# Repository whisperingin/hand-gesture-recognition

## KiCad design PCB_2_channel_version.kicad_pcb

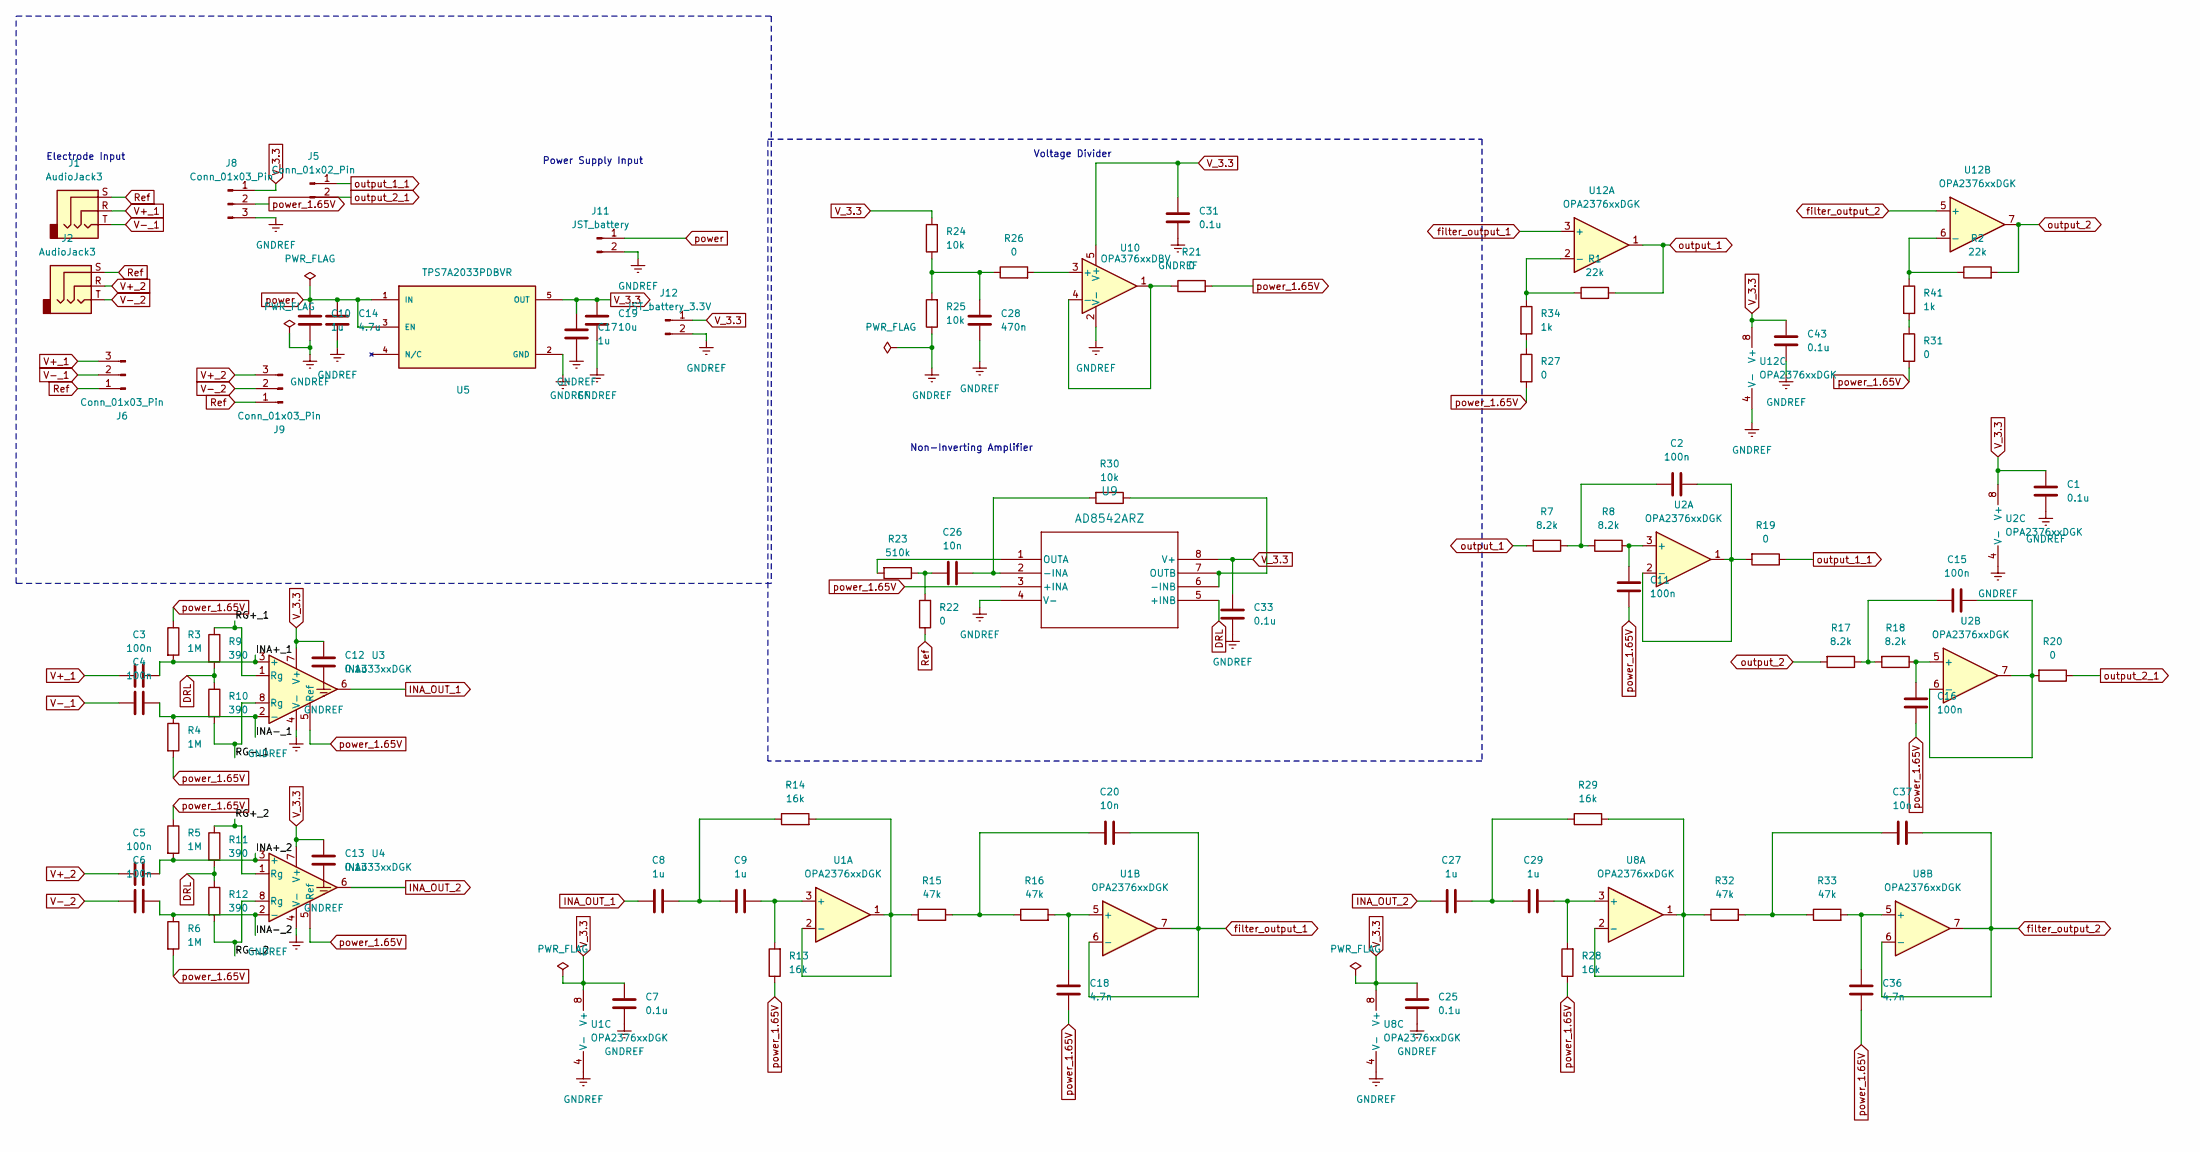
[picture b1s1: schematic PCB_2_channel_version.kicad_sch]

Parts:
C1, C7, C12, C13, C25, C31, C33, C43: 0.1u; C_0603_1608Metric_Pad1.08x0.95mm_HandSolder
C2, C11, C15, C16: 100n; C_0603_1608Metric_Pad1.08x0.95mm_HandSolder
C3, C4, C5, C6: 100n; C_0805_2012Metric_Pad1.18x1.45mm_HandSolder
C8, C9, C10, C17, C27, C29: 1u; C_0805_2012Metric_Pad1.18x1.45mm_HandSolder
C14: 4.7u; C_0805_2012Metric_Pad1.18x1.45mm_HandSolder
C18, C36: 4.7n; C_0805_2012Metric_Pad1.18x1.45mm_HandSolder
C19: 10u; C_0805_2012Metric_Pad1.18x1.45mm_HandSolder
C20, C26, C37: 10n; C_0805_2012Metric_Pad1.18x1.45mm_HandSolder
C28: 470n; C_0603_1608Metric_Pad1.08x0.95mm_HandSolder
J1, J2: AudioJack3; Jack_3.5mm_CUI_SJ-3523-SMT_Horizontal
J5: Conn_01x02_Pin; PinHeader_1x02_P2.54mm_Vertical
J6, J9: Conn_01x03_Pin; JST_PH_S3B-PH-K_1x03_P2.00mm_Horizontal
J8: Conn_01x03_Pin; PinHeader_1x03_P2.54mm_Vertical
J11: JST_battery; JST_PH_B2B-PH-K_1x02_P2.00mm_Vertical
J12: JST_battery_3.3V; JST_PH_B2B-PH-K_1x02_P2.00mm_Vertical
R1, R2: 22k; R_0805_2012Metric_Pad1.20x1.40mm_HandSolder
R3, R4, R5, R6: 1M; R_0805_2012Metric_Pad1.20x1.40mm_HandSolder
R7, R8, R17, R18: 8.2k; R_0603_1608Metric_Pad0.98x0.95mm_HandSolder
R9, R10, R11, R12: 390; R_0805_2012Metric_Pad1.20x1.40mm_HandSolder
R13, R14, R28, R29: 16k; R_0805_2012Metric_Pad1.20x1.40mm_HandSolder
R15, R16, R32, R33: 47k; R_0805_2012Metric_Pad1.20x1.40mm_HandSolder
R19, R20, R21, R22, R26: 0; R_0603_1608Metric_Pad0.98x0.95mm_HandSolder
R23: 510k; R_0805_2012Metric_Pad1.20x1.40mm_HandSolder
R24, R25: 10k; R_0603_1608Metric_Pad0.98x0.95mm_HandSolder
R27, R31: 0; R_0805_2012Metric_Pad1.20x1.40mm_HandSolder
R30: 10k; R_0805_2012Metric_Pad1.20x1.40mm_HandSolder
R34, R41: 1k; R_0805_2012Metric_Pad1.20x1.40mm_HandSolder
U1, U2, U8, U12: OPA2376xxDGK; DGK8
U3, U4: INA333xxDGK; VSSOP-8_3x3mm_P0.65mm
U5: TPS7A2033PDBVR; DBV0005A-IPC_B
U9: AD8542ARZ; R_8_ADI
U10: OPA376xxDBV; SOT-23-5

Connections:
/INA+_1: C3.1, R3.2, U3.3 (+)
/INA+_2: C5.1, R5.2, U4.3 (+)
/INA-_1: C4.1, R4.1, U3.2 (-)
/INA-_2: C6.1, R6.1, U4.2 (-)
/RG+_1: R9.1, U3.1 (Rg)
/RG+_2: R11.1, U4.1 (Rg)
/RG-_1: R10.2, U3.8 (Rg)
/RG-_2: R12.2, U4.8 (Rg)
DRL: R9.2, R10.1, R11.2, R12.1, U9.5 (+INB)
GNDREF: C1.2, C7.2, C10.2, C12.2, C13.2, C14.2, C17.2, C19.2, C25.2, C28.2, C31.2, C33.2, C43.2, J8.3, J11.2, J12.2, R25.1, U1.4 (V-), U2.4 (V-), U3.4 (V-), U4.4 (V-), U5.2 (GND), U8.4 (V-), U9.4 (V-), U10.2 (V-), U12.4 (V-)
INA_OUT_1: C8.2, U3.6
INA_OUT_2: C27.2, U4.6
unnamed: C2.1, R7.1, R8.2
unnamed: C8.1, C9.2, R14.1
unnamed: C15.1, R17.1, R18.2
unnamed: C20.2, R15.2, R16.1
unnamed: C26.2, R22.2, R23.1
unnamed: C27.1, C29.2, R29.1
unnamed: C28.1, R24.1, R25.2, R26.1
unnamed: C37.2, R32.2, R33.1
unnamed: R27.1, R34.2
unnamed: R31.1, R41.2
unnamed: C9.1, R13.2, U1.3 (+)
unnamed: R14.2, R15.1, U1.1, U1.2 (-)
unnamed: C18.1, R16.2, U1.5 (+)
unnamed: C11.2, R8.1, U2.3 (+)
unnamed: C2.2, R19.2, U2.1, U2.2 (-)
unnamed: C16.2, R18.1, U2.5 (+)
unnamed: C15.2, R20.2, U2.6 (-), U2.7
unnamed: C29.1, R28.2, U8.3 (+)
unnamed: R29.2, R32.1, U8.1, U8.2 (-)
unnamed: C36.1, R33.2, U8.5 (+)
unnamed: C26.1, R30.2, U9.2 (-INA)
unnamed: R30.1, U9.6 (-INB), U9.7 (OUTB)
unnamed: R23.2, U9.1 (OUTA)
unnamed: R26.2, U10.3 (+)
unnamed: R21.1, U10.1, U10.4 (-)
unnamed: R1.1, R34.1, U12.2 (-)
unnamed: R2.1, R41.1, U12.6 (-)
Ref: J1.S, J2.S, J6.1, J9.1, R22.1
V+_1: C3.2, J1.R, J6.3
V+_2: C5.2, J2.R, J9.3
V-_1: C4.2, J1.T, J6.2
V-_2: C6.2, J2.T, J9.2
V_3.3: C1.1, C7.1, C12.1, C13.1, C17.1, C19.1, C25.1, C31.1, C33.1, C43.1, J8.1, J12.1, R24.2, U1.8 (V+), U2.8 (V+), U3.7 (V+), U4.7 (V+), U5.5 (OUT), U8.8 (V+), U9.8 (V+), U10.5 (V+), U12.8 (V+)
filter_output_1: C20.1, U1.6 (-), U1.7, U12.3 (+)
filter_output_2: C37.1, U8.6 (-), U8.7, U12.5 (+)
output_1: R1.2, R7.2, U12.1
output_1_1: J5.1, R19.1
output_2: R2.2, R17.2, U12.7
output_2_1: J5.2, R20.1
power: C10.1, C14.1, J11.1, U5.1 (IN), U5.3 (EN)
power_1.65V: C11.1, C16.1, C18.2, C36.2, J8.2, R3.1, R4.2, R5.1, R6.2, R13.1, R21.2, R27.2, R28.1, R31.2, U3.5 (Ref), U4.5 (Ref), U9.3 (+INA)

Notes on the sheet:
Non-Inverting Amplifier
Electrode Input
Power Supply Input
Voltage Divider

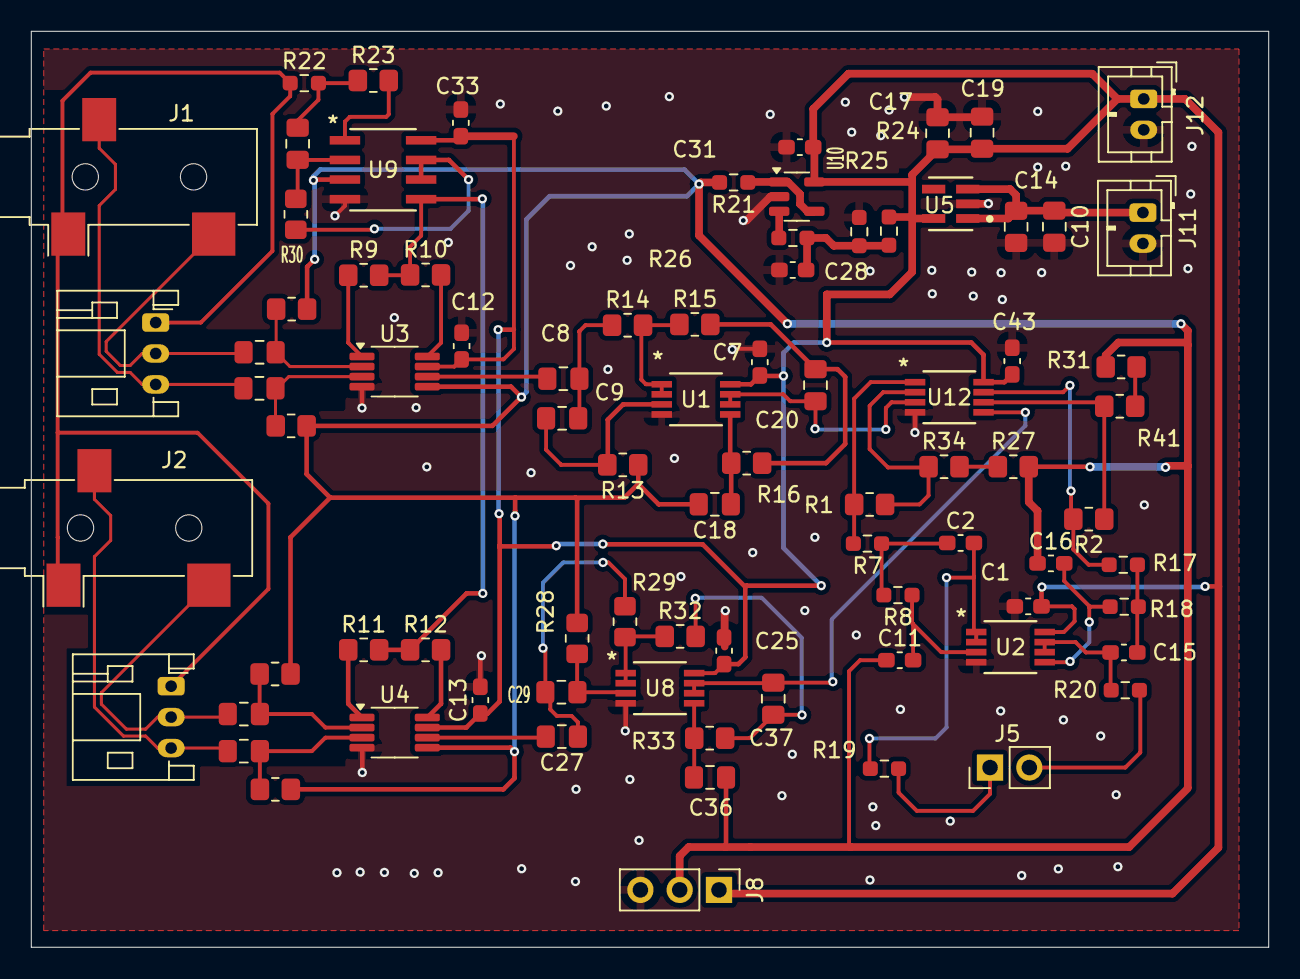
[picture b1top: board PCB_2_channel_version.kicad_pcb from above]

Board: 2 copper layers, 80.0 x 59.2 mm, 82 parts (0 on the bottom side), 53 nets.

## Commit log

2026-03-01 docs: add single-channel CH4 optimization and sEMG denoise guide
2026-03-05 docs: add initial sEMG pipeline diagnostic and required artifacts
